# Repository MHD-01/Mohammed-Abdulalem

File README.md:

# Mohammed-Abdulalem
This is a simple repositry to include what I have acheived and my experience.

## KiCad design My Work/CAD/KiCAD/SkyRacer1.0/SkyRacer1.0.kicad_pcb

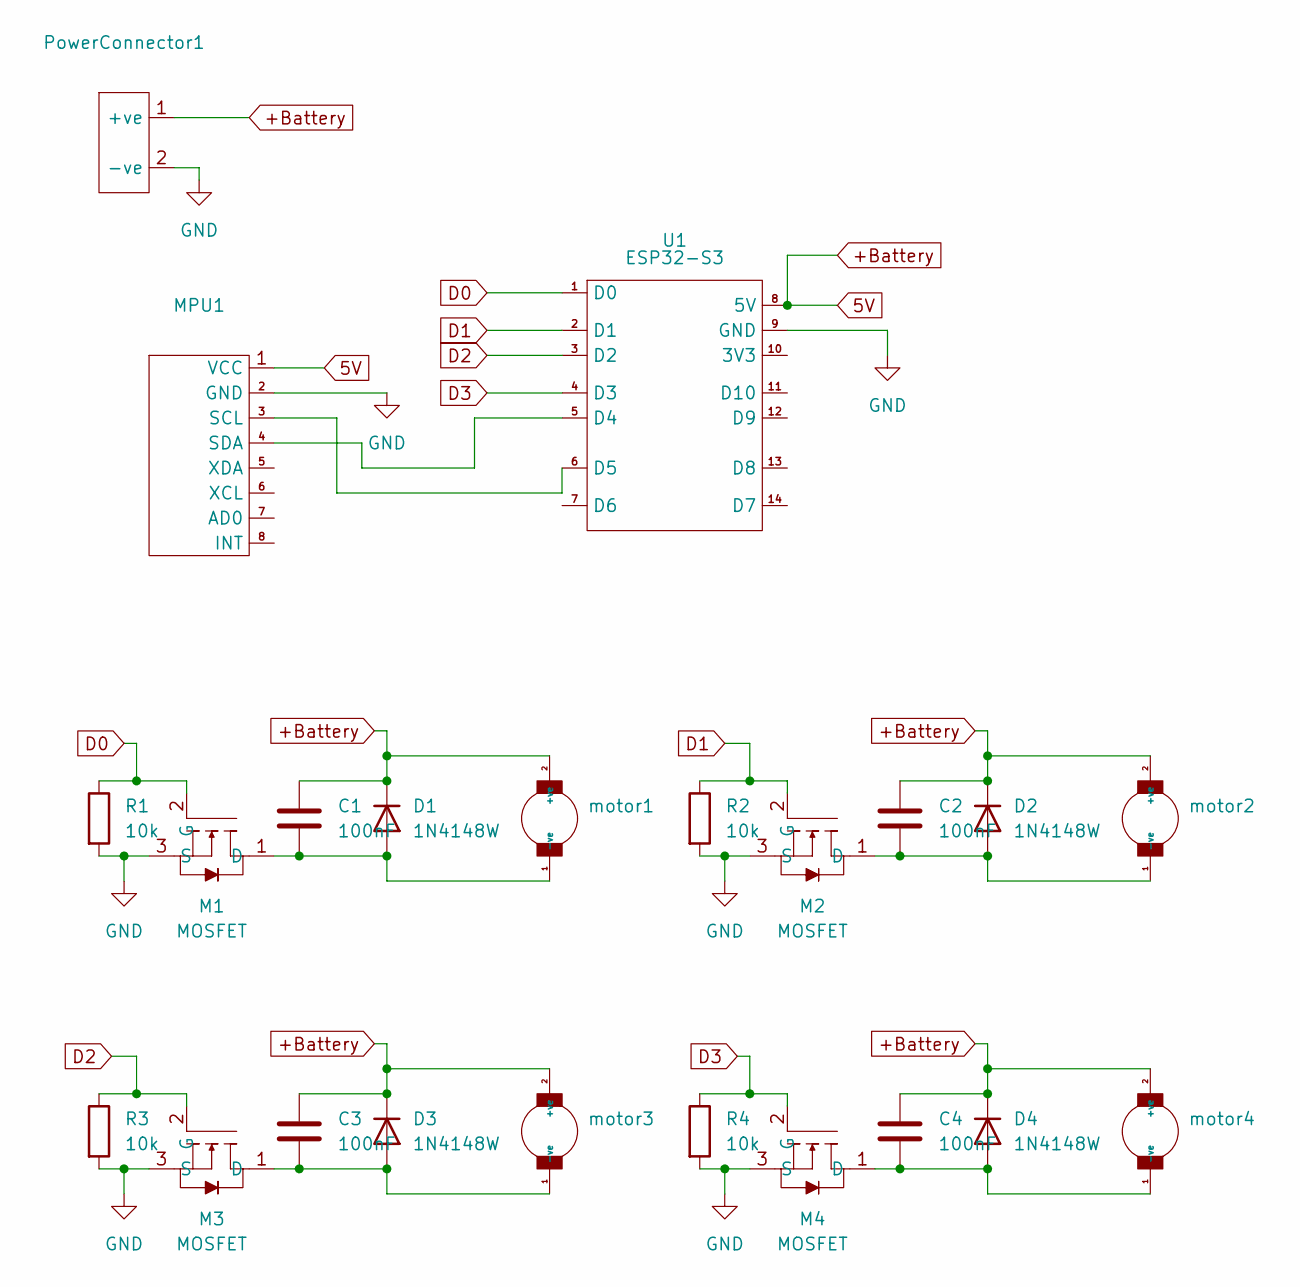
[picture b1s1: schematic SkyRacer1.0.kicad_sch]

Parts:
C1, C2, C3, C4: 100nF; 100nf_c
D1, D2, D3, D4: 1N4148W; 1N4148WT
M1, M2, M3, M4: MOSFET; AO3400A
MPU1: MPU6050
PowerConnector1: PowerConnector
R1, R2, R3, R4: 10k; 10K_R
U1: ESP32-S3; ESP32 S3
motor1, motor2, motor3, motor4: 8250_Motor

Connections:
+Battery: C1.1, C2.1, C3.1, C4.1, D1.1 (K), D2.1 (K), D3.1 (K), D4.1 (K), MPU1.1 (VCC), PowerConnector1.1 (+ve), U1.8 (5V), motor1.2 (+ve), motor2.2 (+ve), motor3.2 (+ve), motor4.2 (+ve)
D0: M1.2 (G), R1.1, U1.1 (D0)
D1: M2.2 (G), R2.1, U1.2 (D1)
D2: M3.2 (G), R3.1, U1.3 (D2)
D3: M4.2 (G), R4.1, U1.4 (D3)
GND: M1.3 (S), M2.3 (S), M3.3 (S), M4.3 (S), MPU1.2 (GND), PowerConnector1.2 (-ve), R1.2, R2.2, R3.2, R4.2, U1.9 (GND)
unnamed: C1.2, D1.2 (A), M1.1 (D), motor1.1 (-ve)
unnamed: C2.2, D2.2 (A), M2.1 (D), motor2.1 (-ve)
unnamed: C3.2, D3.2 (A), M3.1 (D), motor3.1 (-ve)
unnamed: C4.2, D4.2 (A), M4.1 (D), motor4.1 (-ve)
unnamed: MPU1.3 (SCL), U1.6 (D5)
unnamed: MPU1.4 (SDA), U1.5 (D4)

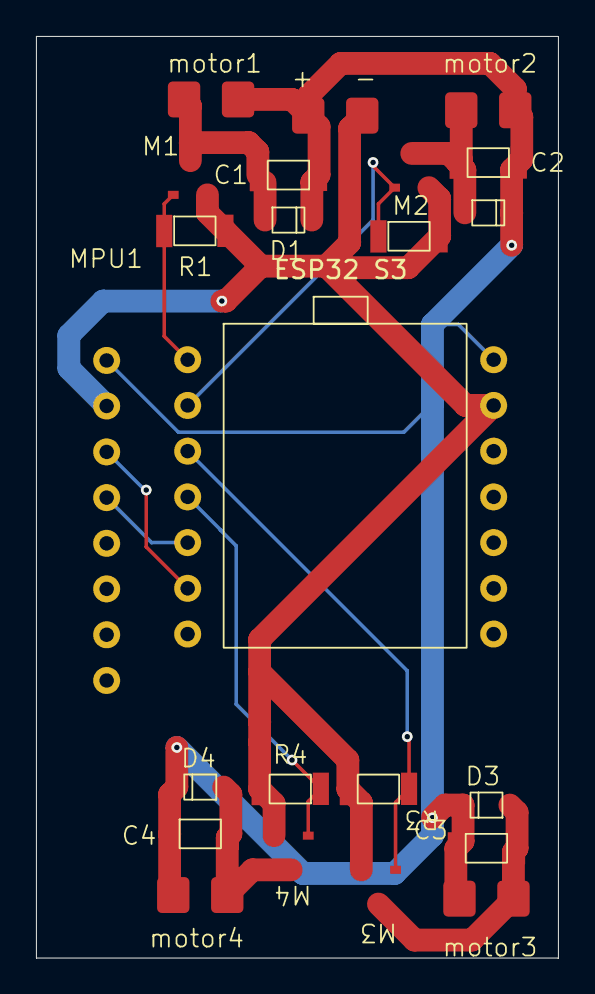
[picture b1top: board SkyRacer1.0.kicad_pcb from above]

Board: 2 copper layers, 29.0 x 51.2 mm, 23 parts (0 on the bottom side), 12 nets.
